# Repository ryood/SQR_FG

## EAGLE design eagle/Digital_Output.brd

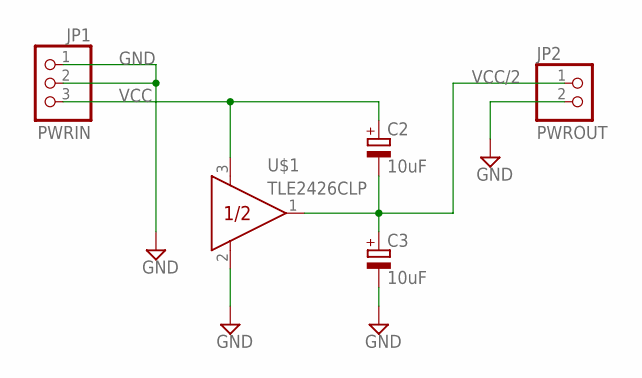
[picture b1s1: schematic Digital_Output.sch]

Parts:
C2, C3: 10uF; E2,5-5
JP1: PWRIN; 1X03
JP2: PWROUT; 1X02
U$1: TLE2426CLP; TO226AA

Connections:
GND: C3.-, JP1.1, JP1.2, JP2.2, U$1.2 (COM)
VCC: C2.+, JP1.3, U$1.3 (IN)
VCC/2: C2.-, C3.+, JP2.1, U$1.1 (OUT)

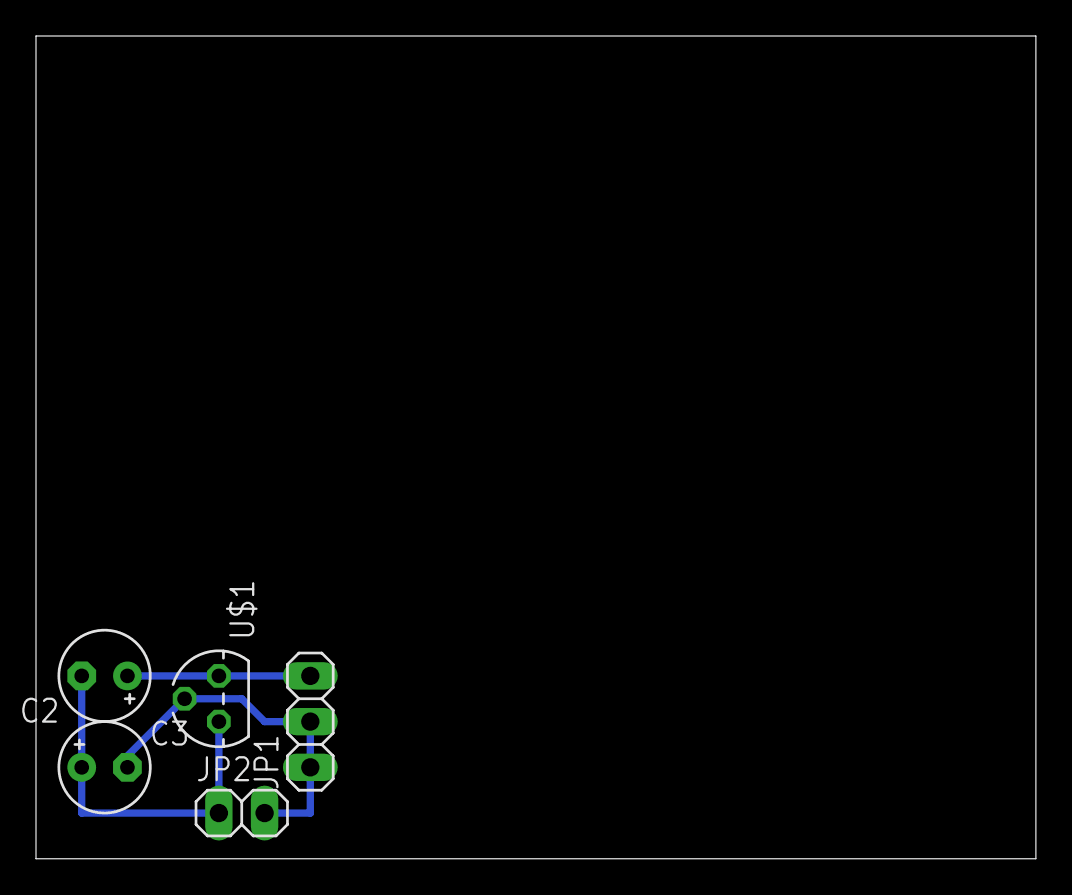
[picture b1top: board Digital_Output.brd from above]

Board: 2 copper layers, 55.5 x 45.7 mm, 5 parts (0 on the bottom side), 3 nets.

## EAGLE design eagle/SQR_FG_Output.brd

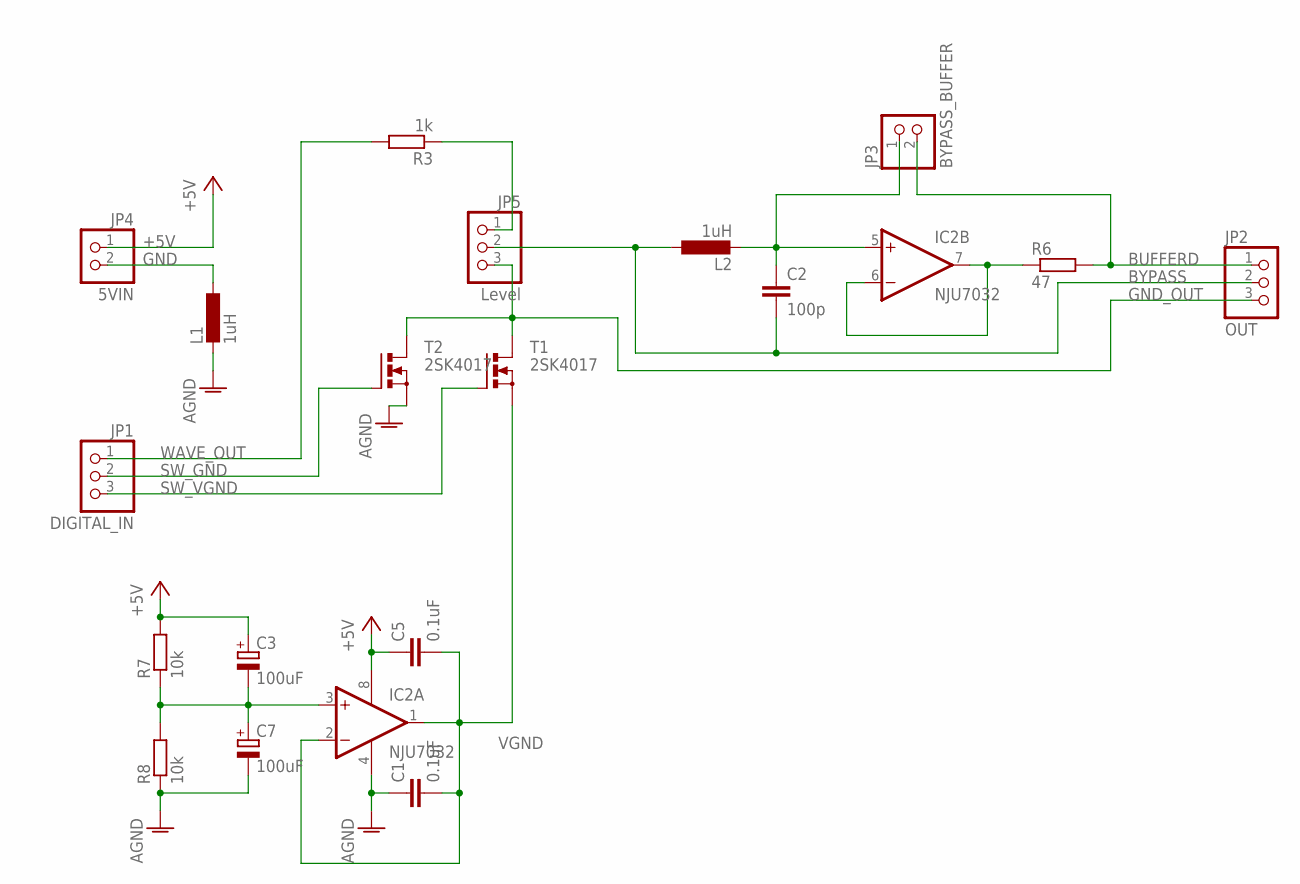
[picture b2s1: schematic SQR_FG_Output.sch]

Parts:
C1, C5: 0.1uF; C025-024X044
C2: 100p; C075-032X103
C3, C7: 100uF; E2,5-5
IC2: NJU7032; DIL08
JP1: DIGITAL_IN; 1X03
JP2: OUT; 1X03
JP3: BYPASS_BUFFER; 1X02
JP4: 5VIN; 1X02
JP5: Level; 1X03
L1, L2: 1uH; 0204/7
R3: 1k; 0207/7
R6: 47; 0207/7
R7, R8: 10k; 0207/7
T1, T2: 2SK4017; TO220BV

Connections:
+5V: C3.+, C5.1, IC2.8 (V+), JP4.1, R7.2
AGND: C1.1, C7.-, IC2.4 (V-), L1.2, R8.1, T2.S
BUFFERD: JP2.1, JP3.2, R6.2
BYPASS: C2.2, JP2.2, JP5.2, L2.1
GND: JP4.2, L1.1
GND_OUT: JP2.3, JP5.3, T1.D, T2.D
unnamed: C2.1, IC2.5 (+IN), JP3.1, L2.2
unnamed: JP5.1, R3.1
unnamed: IC2.6 (-IN), IC2.7 (OUT), R6.1
unnamed: C3.-, C7.+, IC2.3 (+IN), R7.1, R8.2
SW_GND: JP1.2, T2.G
SW_VGND: JP1.3, T1.G
VGND: C1.2, C5.2, IC2.1 (OUT), IC2.2 (-IN), T1.S
WAVE_OUT: JP1.1, R3.2

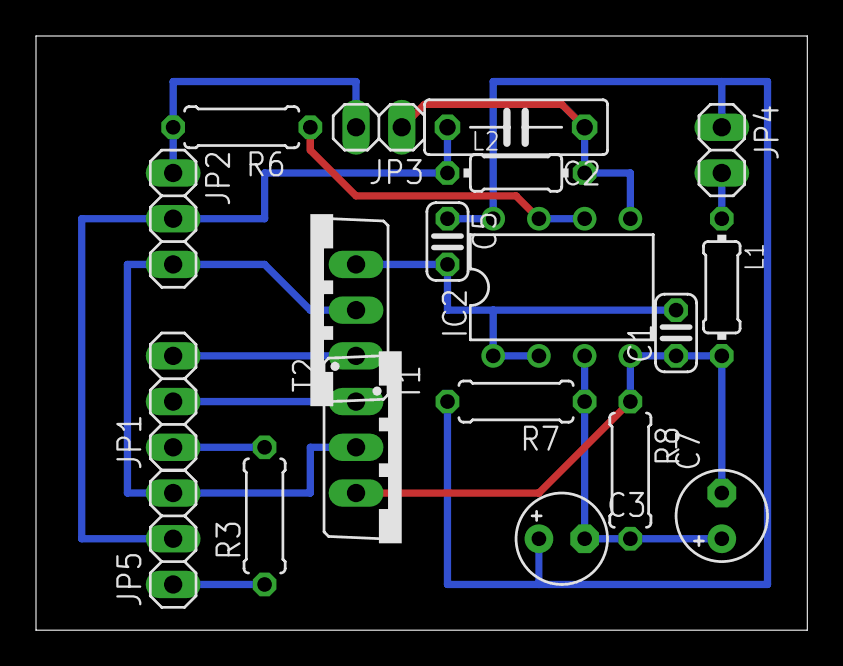
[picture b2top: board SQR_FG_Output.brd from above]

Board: 2 copper layers, 42.9 x 33.0 mm, 19 parts (0 on the bottom side), 14 nets.

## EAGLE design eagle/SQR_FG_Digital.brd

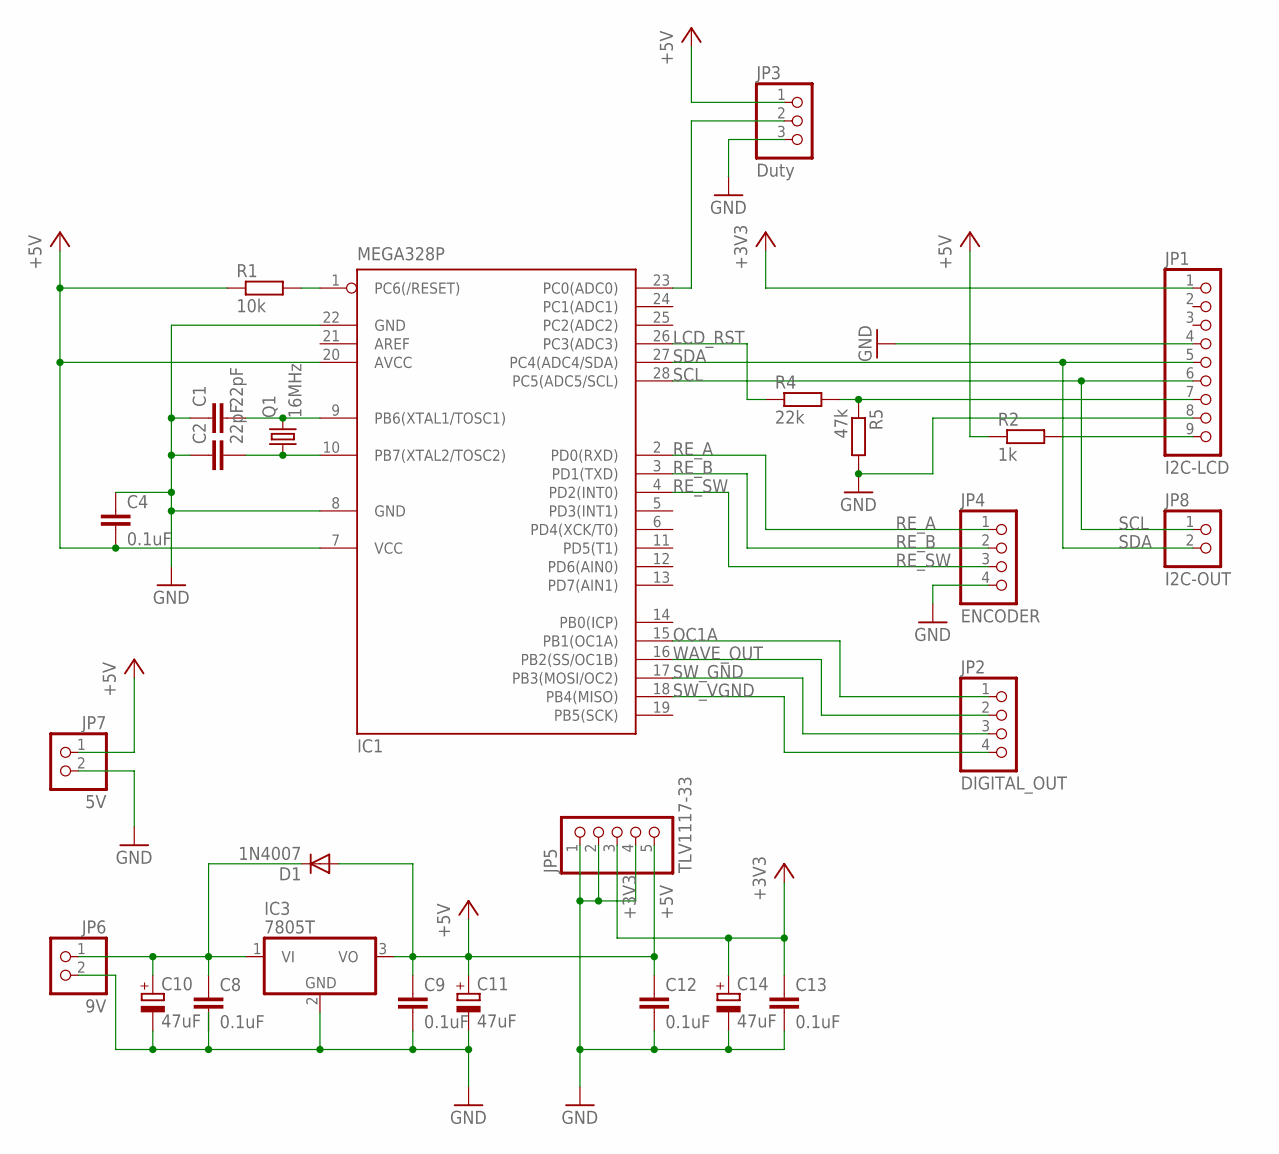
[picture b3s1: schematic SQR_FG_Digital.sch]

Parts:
C1, C2: 22pF; C050-024X044
C4, C8, C9, C12, C13: 0.1uF; C025-024X044
C10, C11, C14: 47uF; TT2D5L
D1: 1N4007; DO41-10
IC1: MEGA328P; DIL28-3
IC3: 7805T; TO220H
JP1: I2C-LCD; 1X09
JP2: DIGITAL_OUT; 1X04
JP3: Duty; 1X03
JP4: ENCODER; 1X04
JP5: TLV1117-33; 1X05
JP6: 9V; 1X02
JP7: 5V; 1X02
JP8: I2C-OUT; 1X02
Q1: 16MHz; HC49/S
R1: 10k; 0207/10
R2: 1k; 0207/7
R4: 22k; 0207/7
R5: 47k; 0207/7

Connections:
+3V3: C13.1, C14.+, JP1.1, JP5.3
+5V: C4.2, C9.1, C11.+, C12.1, D1.A, IC1.7 (VCC), IC1.20 (AVCC), IC3.3 (VO), JP3.1, JP5.5, JP7.1, R1.1, R2.1
GND: C1.1, C2.1, C4.1, C8.2, C9.2, C10.-, C11.-, C12.2, C13.2, C14.-, IC1.8 (GND), IC1.22 (GND), IC3.2 (GND), JP1.4, JP1.8, JP3.3, JP4.4, JP5.1, JP5.2, JP5.4, JP6.2, JP7.2, R5.2
LCD_RST: IC1.26 (PC3(ADC3)), R4.1
unnamed: C1.2, IC1.9 (PB6(XTAL1/TOSC1)), Q1.2
unnamed: C2.2, IC1.10 (PB7(XTAL2/TOSC2)), Q1.1
unnamed: IC1.1 (PC6(/RESET)), R1.2
unnamed: C8.1, C10.+, D1.C, IC3.1 (VI), JP6.1
unnamed: JP1.9, R2.2
unnamed: IC1.23 (PC0(ADC0)), JP3.2
OC1A: IC1.15 (PB1(OC1A)), JP2.1
RE_A: IC1.2 (PD0(RXD)), JP4.1
RE_B: IC1.3 (PD1(TXD)), JP4.2
RE_SW: IC1.4 (PD2(INT0)), JP4.3
RST: JP1.7, R4.2, R5.1
SCL: IC1.28 (PC5(ADC5/SCL)), JP1.6, JP8.1
SDA: IC1.27 (PC4(ADC4/SDA)), JP1.5, JP8.2
SW_GND: IC1.17 (PB3(MOSI/OC2)), JP2.3
SW_VGND: IC1.18 (PB4(MISO)), JP2.4
WAVE_OUT: IC1.16 (PB2(SS/OC1B)), JP2.2

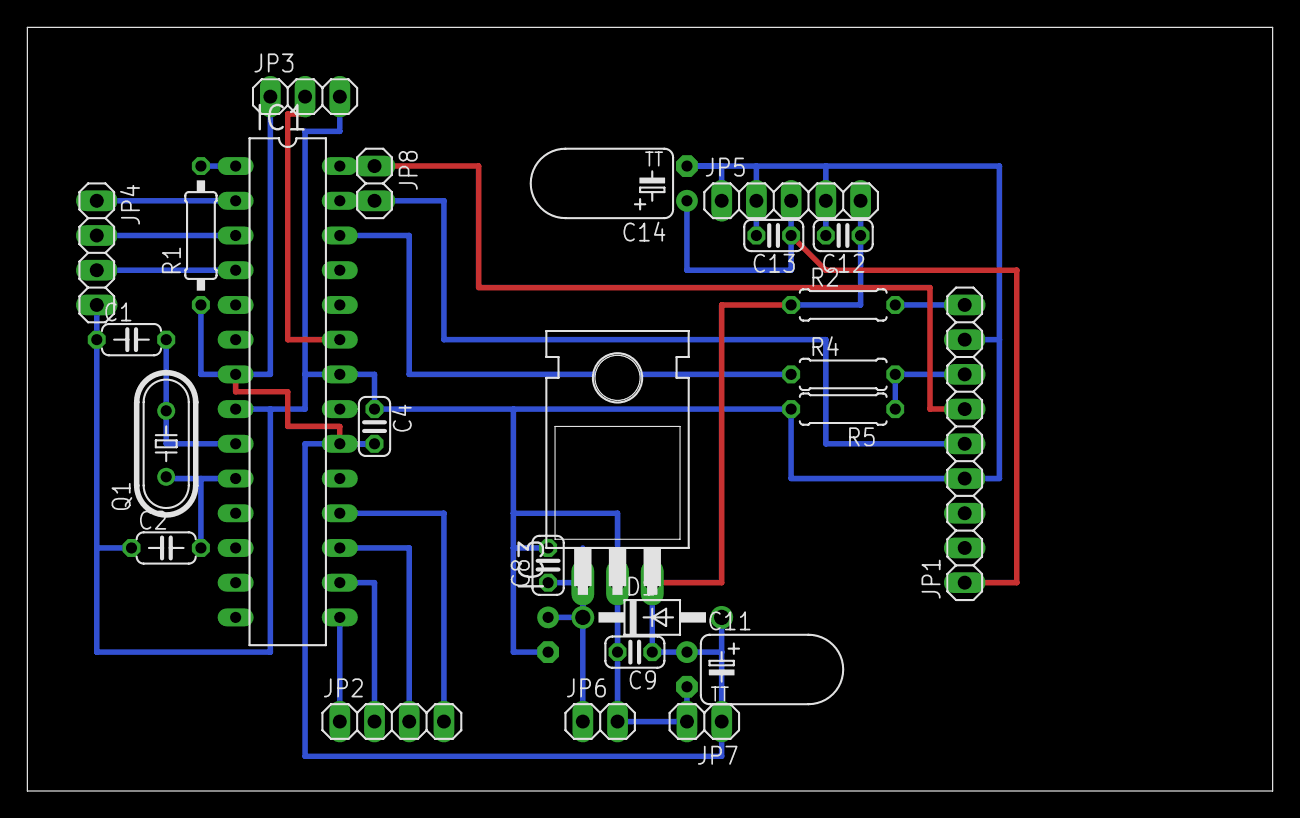
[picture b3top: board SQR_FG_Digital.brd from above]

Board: 2 copper layers, 91.1 x 55.9 mm, 26 parts (1 on the bottom side), 20 nets.

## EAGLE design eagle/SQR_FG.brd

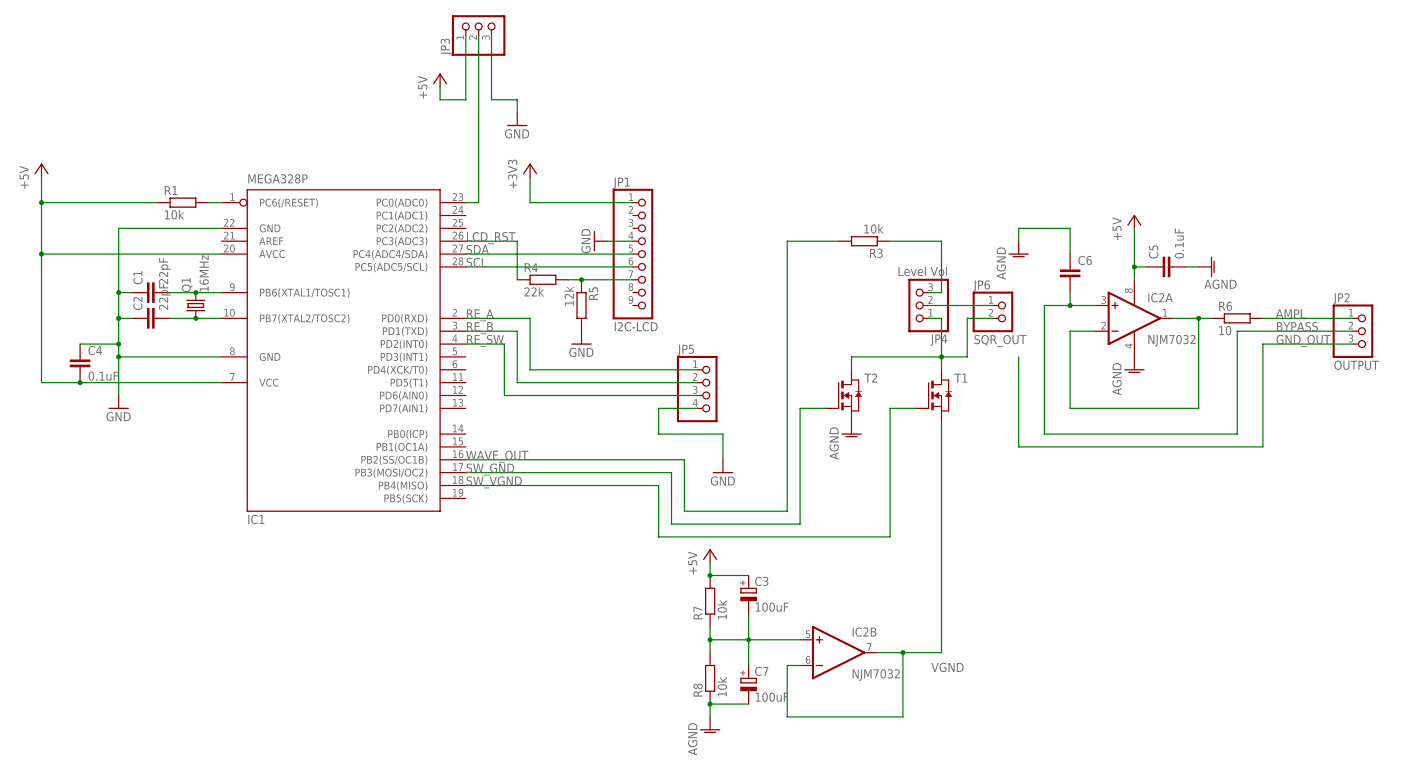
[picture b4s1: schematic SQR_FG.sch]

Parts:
C1, C2: 22pF; C025-024X044
C3, C7: 100uF; E2,5-5
C4, C5: 0.1uF; C025-024X044
C6: C-EU025-024X044; C025-024X044
IC1: MEGA328P; DIL28-3
IC2: NJM7032; DIL08
JP1: I2C-LCD; 1X09
JP2: OUTPUT; 1X03
JP3: PINHD-1X3; 1X03
JP4: Level Vol; 1X03
JP5: PINHD-1X4; 1X04
JP6: SQR_OUT; 1X02
Q1: 16MHz; HC49/S
R1, R3, R7, R8: 10k; 0207/7
R4: 22k; 0207/7
R5: 12k; 0207/7
R6: 10; 0207/7
T1, T2: NMOSE3L; E3LINE

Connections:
+3V3: JP1.1
+5V: C3.+, C4.2, C5.1, IC1.7 (VCC), IC1.20 (AVCC), IC2.8 (V+), JP3.1, R1.1, R7.2
AGND: C5.2, C6.1, C7.-, IC2.4 (V-), R8.1, T2.3 (S)
AMPL: JP2.1, R6.2
BYPASS: C6.2, IC2.3 (+IN), JP2.2
GND: C1.1, C2.1, C4.1, IC1.8 (GND), IC1.22 (GND), JP1.4, JP3.3, JP5.4, R5.2
GND_OUT: JP2.3
LCD_RST: IC1.26 (PC3(ADC3)), R4.1
unnamed: C1.2, IC1.9 (PB6(XTAL1/TOSC1)), Q1.2
unnamed: C2.2, IC1.10 (PB7(XTAL2/TOSC2)), Q1.1
unnamed: IC1.1 (PC6(/RESET)), R1.2
unnamed: JP4.2, JP6.1
unnamed: JP4.1, JP6.2, T1.1 (D), T2.1 (D)
unnamed: JP4.3, R3.1
unnamed: IC1.23 (PC0(ADC0)), JP3.2
unnamed: IC2.1 (OUT), IC2.2 (-IN), R6.1
unnamed: C3.-, C7.+, IC2.5 (+IN), R7.1, R8.2
RE_A: IC1.2 (PD0(RXD)), JP5.1
RE_B: IC1.3 (PD1(TXD)), JP5.2
RE_SW: IC1.4 (PD2(INT0)), JP5.3
RST: JP1.7, R4.2, R5.1
SCL: IC1.28 (PC5(ADC5/SCL)), JP1.6
SDA: IC1.27 (PC4(ADC4/SDA)), JP1.5
SW_GND: IC1.17 (PB3(MOSI/OC2)), T2.2 (G)
SW_VGND: IC1.18 (PB4(MISO)), T1.2 (G)
VGND: IC2.6 (-IN), IC2.7 (OUT), T1.3 (S)
WAVE_OUT: IC1.16 (PB2(SS/OC1B)), R3.2

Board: 2 copper layers, 25 parts (0 on the bottom side), 25 nets, no tracks yet.

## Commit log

2015-05-11 Add Eagle files
2015-05-11 eagle: Add Bypass Connector
2015-05-11 Add LTSpice & Fritzing files
2015-05-11 Add MOS-FET Switching
2015-05-11 Change eagle SQR_FG.sch R value
2015-05-11 SQR_FG.c: implement Rotary Encoder SW GND or VGND
2015-05-14 SQR_FG_Test.fzz Update
2015-05-14 SQR_FG_Test.fzz: Update
2015-05-14 SQR_FG.c: impliment I2C-LCD, Bug fix cycle bound bug
2015-05-14 before editing SQR_FG.brd
2015-05-17 SQR_FG.brd SQR_FG board design editing.
2015-05-17 eagle files: デジタル部と出力部に基板を分割
2015-05-26 SQR_FG_Digital: I2Cの信号をピンソケットで出力できるように変更
2015-05-26 fritzingにケース内配線図を追加
2015-05-28 SQR_FG_Digital.sch: LCDのRST信号の分圧抵抗を変更
2015-05-28 SQR_FG.c: SQR WAV, Impulse, Stepの実装OK
2015-05-28 SQR_FG.c: for Relese version
2015-06-02 SQR_FG_ケース内配線.fzz 修正
2015-06-03 SQR_FG.c 初期周波数を1000Hzに変更
2015-06-03 SQR_FG_Output.sch LC 2次LPFを追加
2015-06-06 ケース内配線図： ケーブルの色を変更
2015-06-06 SQR_FG_Output.sch, brd: MOS-FETのGate, Drain, Sourceの並びを修正
2015-06-10 SQR_FG_ケース内配線.fzz: 出力用のStereominiプラグを2系統に変更
2015-06-10 cad¥: ケース加工図を追加
2015-06-10 SQR_FG_Case.dwg: Update
2015-06-21 SQR_FG_Case.dwg: ケース加工図修正
2015-06-21 テスト表追加
2015-09-17 Add: LogicIC-Filter.zip
2015-11-23 出力部をシンプルにする作業開始 不要ファイルを削除
2015-11-23 SQR_FG_ケース内配線.fzz: シンプル出力部に修正
2015-12-02 ファームウェアの修正開始
2015-12-03 SQR_FG.c: 矩形波出力を実装（プリスケーラーはまだ）
2015-12-03 SQR_FG.c: プリスケーラを実装
2015-12-03 SQR_FG.c: ロータリーエンコーダーのチャタリング対策
2015-12-04 Ver.2 動作OK、参考図追加
2015-12-04 Version 2
2015-12-04 出力部のEagleファイルを変更
2015-12-04 デジタル部の回路図、基板図のPNGファイルを追加
2015-12-04 Add: SQR_FG_出力周波数表.xlsx
